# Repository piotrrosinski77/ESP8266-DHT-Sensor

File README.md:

# ESP8266-DHT-Sensor
This project enables wireless monitoring of temperature and humidity using a DHT sensor connected to an ESP8266 microcontroller. The ESP8266 collects real-time data from the DHT sensor and transmits it over Wi-Fi, allowing you to access the data through a web interface using HTML.

## Features
- Real-Time Data Collection: Reads temperature and humidity values from the DHT sensor at regular intervals.
- Wireless Transmission: Uses Wi-Fi to send data to a web interface or a remote server.
- Remote Monitoring: Access the sensor data on any device connected to the same network or via the internet if configured.

## Web server (via IP Address)
ESP8266 acts as a web server providing the readings from the DHT sensor (e.g., DHT11 or DHT22).
<div align="left">
    
</div>

## Hardware Requirements (breadboard)
- ESP8266 Microcontroller
- DHT Sensor (e.g., DHT11 or DHT22)
- LCD HD44780 16x2 or 20x4
- I2C apapter for LCD 
- Jumper Wires
- Breadboard
- LED
- 4.7 kΩ Resistor
- 220 kΩ Resistor
<div align="left">
    
</div>

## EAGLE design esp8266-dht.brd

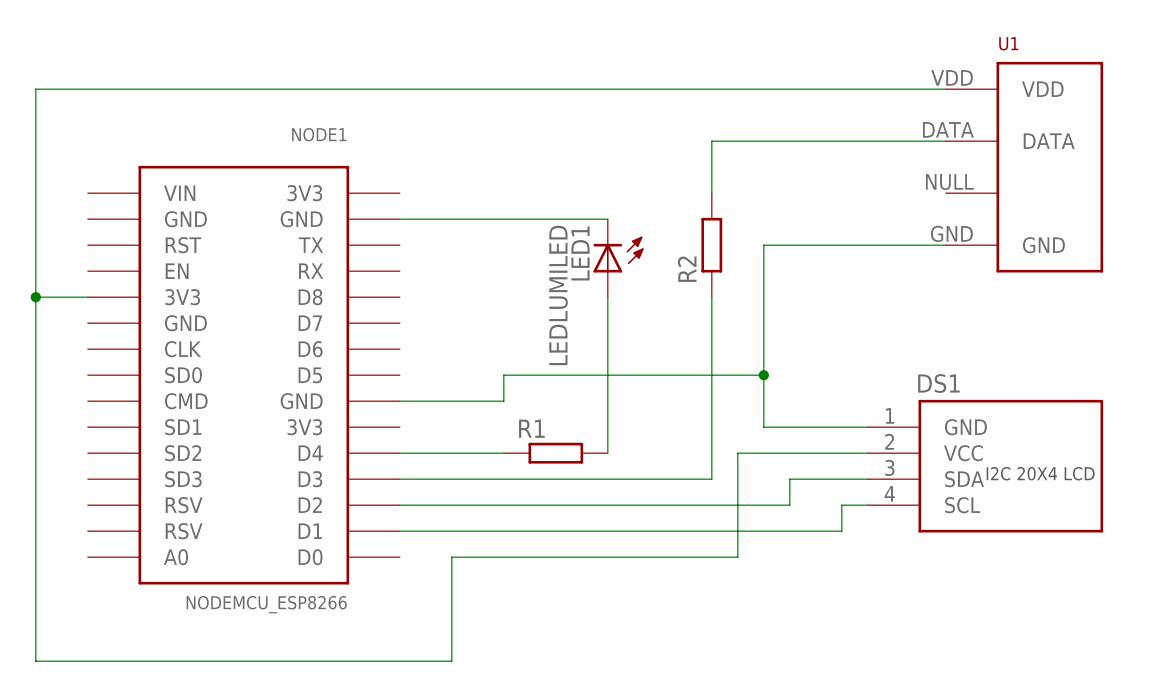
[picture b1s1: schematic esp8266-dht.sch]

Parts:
DS1: LCD-20X4I2C
LED1: LEDLUMILED; LUMILED
NODE1: NODEMCU_ESP8266
R1, R2: R-EU_0204/7; 0204/7
U1: RHT03_DHT-22_AM2302RA; RHT03_DHT-22/RA

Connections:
3V3: NODE1.3V3@1 (3V3), NODE1.3V3@2 (3V3)
GND: NODE1.GND@3 (GND), NODE1.GND@4 (GND)
unnamed: NODE1.D4, R1.1
unnamed: LED1.2+ (A), R1.2
unnamed: LED1.4- (C), NODE1.GND@1 (GND)
unnamed: NODE1.D3, R2.1
unnamed: R2.2, U1.DATA
unnamed: DS1.2 (VCC), NODE1.3V3@3 (3V3), U1.VDD
unnamed: DS1.1 (GND), NODE1.GND@2 (GND), U1.GND
unnamed: DS1.3 (SDA), NODE1.D2
unnamed: DS1.4 (SCL), NODE1.D1
VIN: NODE1.VIN

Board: 2 copper layers, 6 parts (0 on the bottom side), 11 nets, no tracks yet.

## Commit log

2024-10-22 added main file&brd&sch&i2c_adapter(to do)
2024-10-24 better not to ask
2024-10-26 deleted unnecessary file
2024-10-26 prepared the code for 20x4 LCD
2024-10-26 added photos
2024-10-27 minor changes
2024-10-29 added LICENSE
